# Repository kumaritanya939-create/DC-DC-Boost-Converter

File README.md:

# DC-DC-Boost-Converter
Designed and developed a DC-DC Boost Converter PCB to efficiently step up low input voltage to a higher regulated output voltage. Created the schematic, PCB layout, and validated the design through simulation and testing using KiCad/Altium Designer.

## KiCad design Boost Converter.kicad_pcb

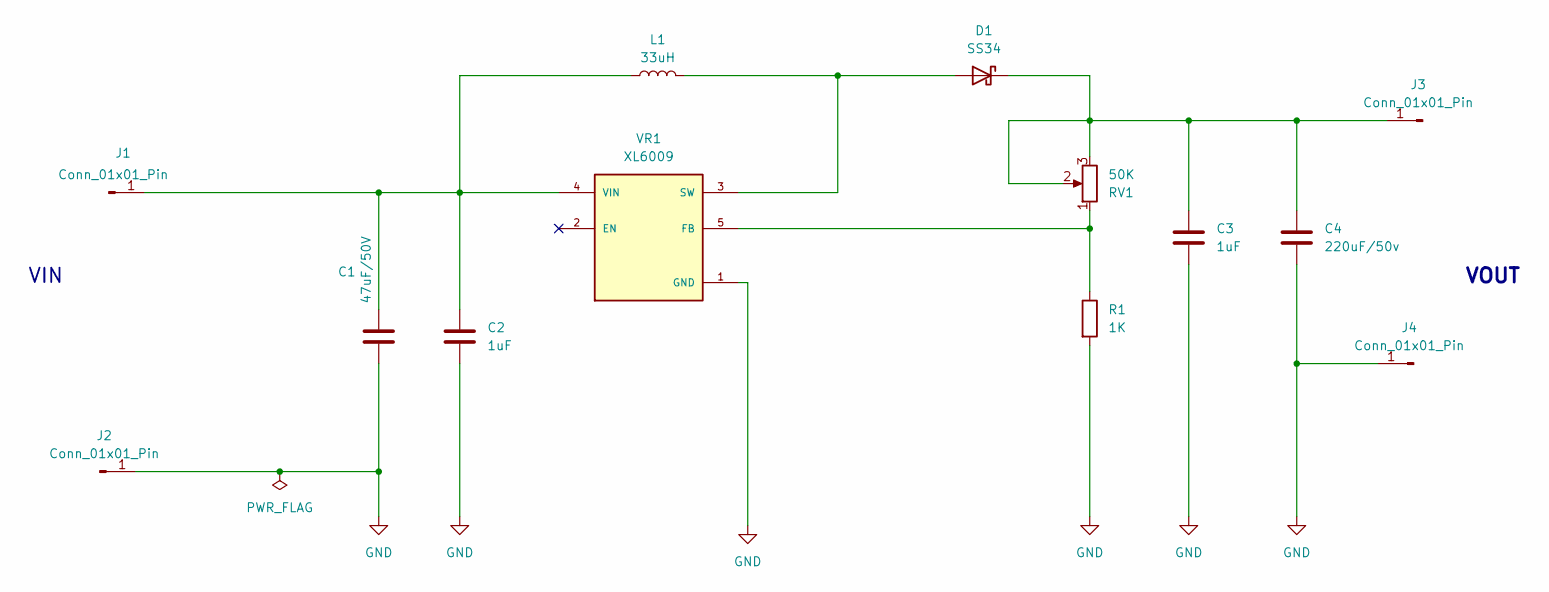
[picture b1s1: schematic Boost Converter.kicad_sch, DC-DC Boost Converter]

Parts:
C1: 47uF/50V; C_Radial_D8.0mm_H7.0mm_P3.50mm
C2, C3: 1uF; C_0805_2012Metric
C4: 220uF/50v; C_Radial_D8.0mm_H7.0mm_P3.50mm
D1: SS34; D_SMA
J1, J2, J3, J4: Conn_01x01_Pin; PinHeader_1x01_P2.54mm_Vertical
L1: 33uH; L_12x12mm_H8mm
R1: 1K; R_1206_3216Metric
RV1: 50K; Potentiometer_Bourns_3296W_Vertical
VR1: XL6009; DPAK170P1435X465-6N; PARTREV 1.1

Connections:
GND: C1.2, C2.2, C3.2, C4.2, J2.1 (Pin_1_1), J4.1 (Pin_1_1), R1.2, VR1.1 (GND)
unnamed: D1.2 (A), L1.2, VR1.3 (SW), VR1.6 (SW)
unnamed: C3.1, C4.1, D1.1 (K), J3.1 (Pin_1_1), RV1.2, RV1.3
unnamed: C1.1, C2.1, J1.1 (Pin_1_1), L1.1, VR1.4 (VIN)
unnamed: R1.1, RV1.1, VR1.5 (FB)

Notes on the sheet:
VIN
VOUT

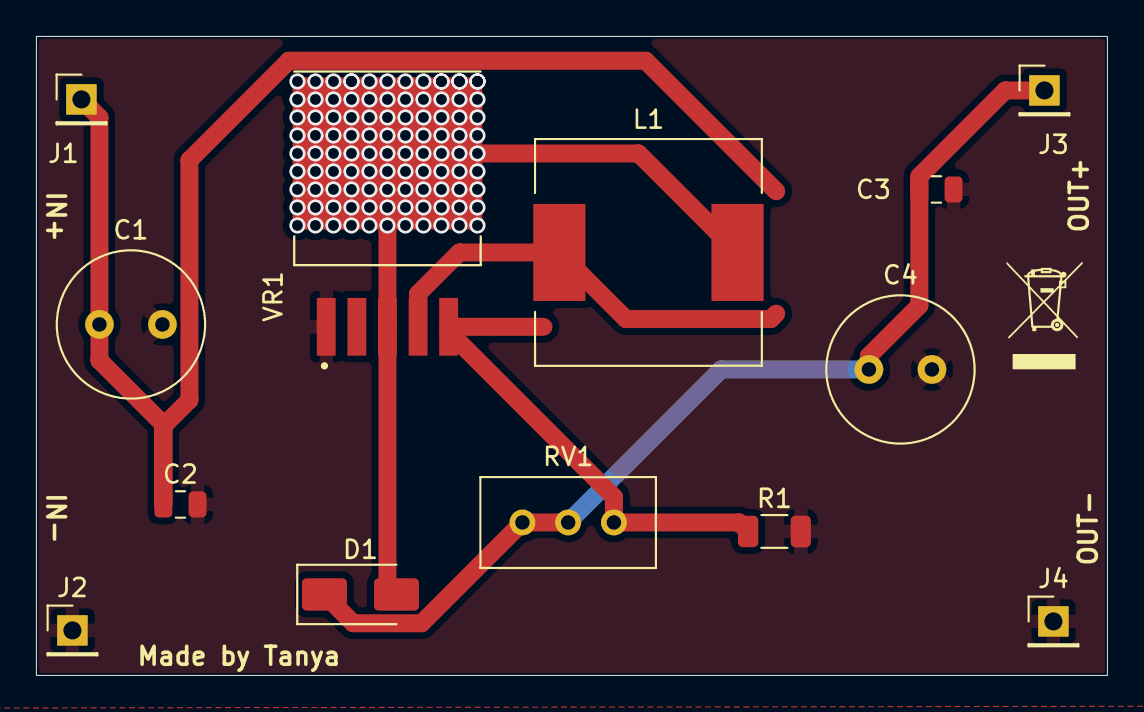
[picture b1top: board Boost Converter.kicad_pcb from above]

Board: 2 copper layers, 59.5 x 35.5 mm, 13 parts (0 on the bottom side), 5 nets.
